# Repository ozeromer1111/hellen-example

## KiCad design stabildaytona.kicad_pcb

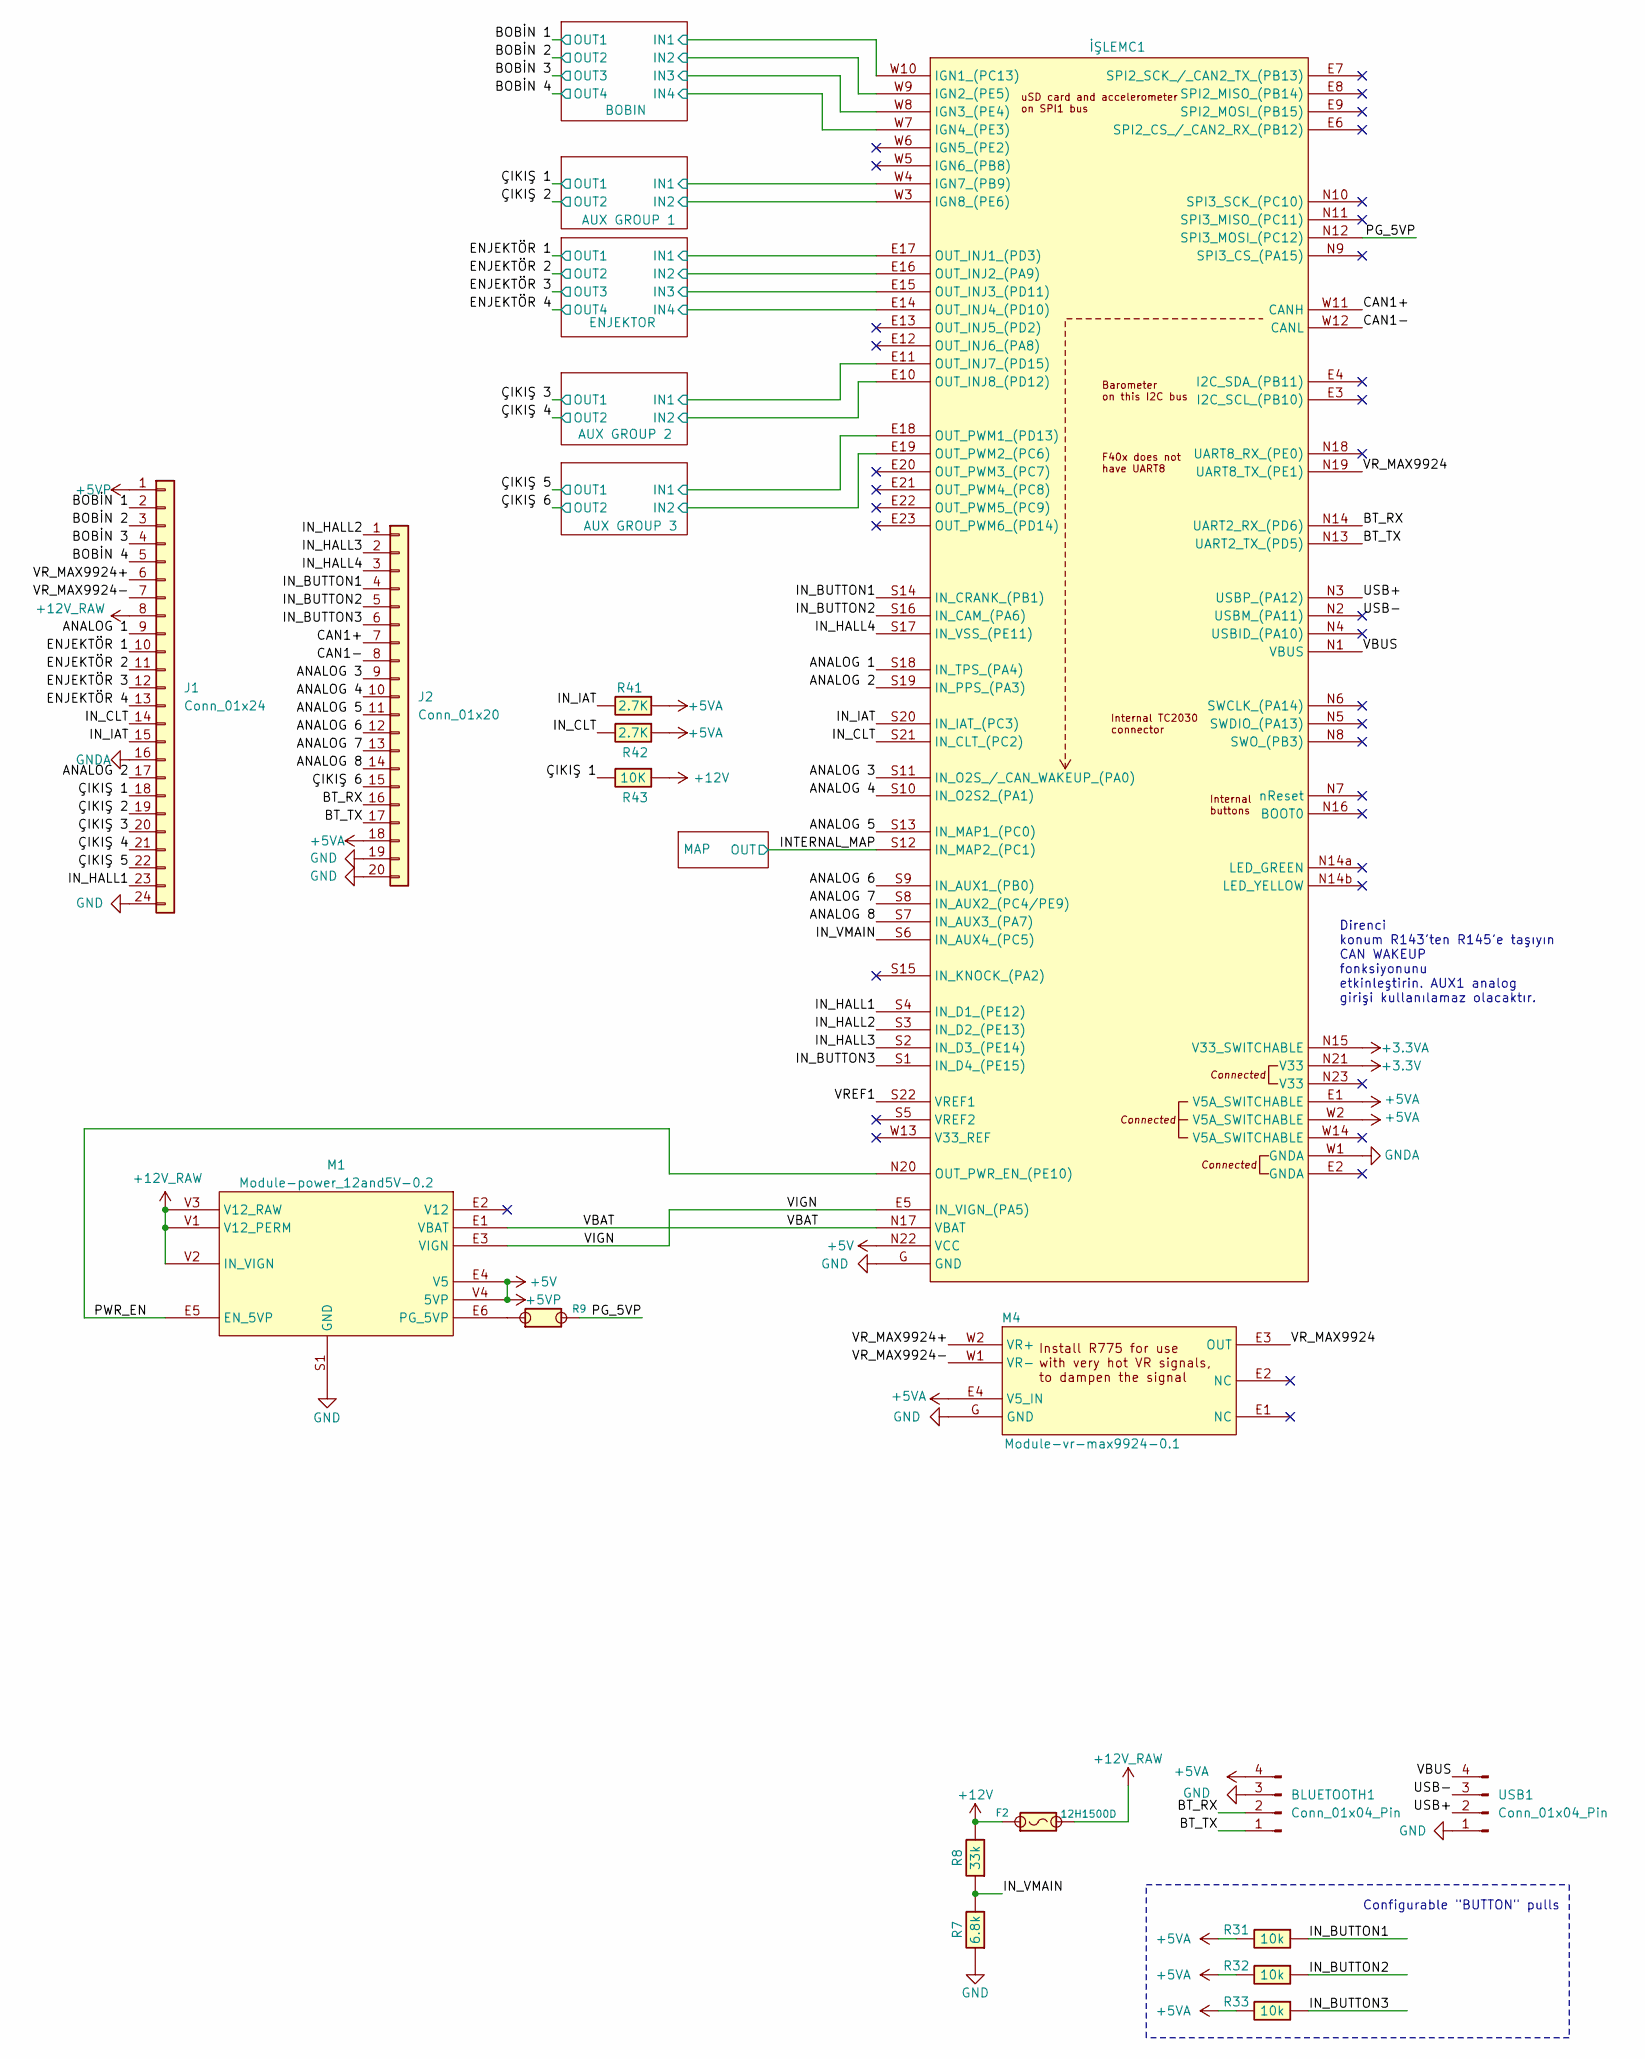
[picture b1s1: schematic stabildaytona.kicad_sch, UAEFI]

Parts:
BLUETOOTH1: Conn_01x04_Pin; PinSocket_1x04_P2.54mm_Vertical; LCSC C22438154
F2: 12H1500D; PAD-1206-PAD; LCSC C182446
J1: Conn_01x24; 24pin
J2: Conn_01x20; TE_2-826576-0_1x20_P3.96mm_Vertical
M1: Module-power_12and5V-0.2; power_12and5V
M4: Module-vr-max9924-0.1; vr-max9924
R7: 6.8k; R0603; LCSC C23212
R8: 33k; R0603; LCSC C4216
R9: Jumper-Pad-Pad; PAD-0805-PAD; LCSC C17477
R31, R32, R33: 10k; R0805; LCSC C17414
R41, R42: 2.7K; R0805; LCSC C17414
R43: 10K; R0805; LCSC C17414
USB1: Conn_01x04_Pin; JST_PH_B4B-PH-K_1x04_P2.00mm_Vertical; LCSC C265289
İŞLEMC1: Module:mega-mcu100/0.3; mega-mcu100

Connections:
+3.3V: İŞLEMC1.N21 (V33)
+3.3VA: İŞLEMC1.N15 (V33_SWITCHABLE)
+5V: J1.1, M1.E4 (V5), M1.V4 (5VP), İŞLEMC1.N22 (VCC)
+5VA: BLUETOOTH1.4, J2.18, M4.E4 (V5_IN), R31.2, R32.2, R33.2, R41.1, R42.1, İŞLEMC1.E1 (V5A_SWITCHABLE), İŞLEMC1.W2 (V5A_SWITCHABLE); also elsewhere on the board
+12V: F2.1, R8.2, R43.1
+12V_RAW: F2.2, J1.8, M1.V1 (V12_PERM), M1.V2 (IN_VIGN), M1.V3 (V12_RAW)
/ANALOG 1: J1.9, İŞLEMC1.S18 (IN_TPS_(PA4))
/ANALOG 2: J1.17, İŞLEMC1.S19 (IN_PPS_(PA3))
/ANALOG 3: J2.9, İŞLEMC1.S11 (IN_O2S_/_CAN_WAKEUP_(PA0))
/ANALOG 4: J2.10, İŞLEMC1.S10 (IN_O2S2_(PA1))
/ANALOG 5: J2.11, İŞLEMC1.S13 (IN_MAP1_(PC0))
/ANALOG 6: J2.12, İŞLEMC1.S9 (IN_AUX1_(PB0))
/ANALOG 7: J2.13, İŞLEMC1.S8 (IN_AUX2_(PC4/PE9))
/ANALOG 8: J2.14, İŞLEMC1.S7 (IN_AUX3_(PA7))
/AUX GROUP 1/IN1: İŞLEMC1.W4 (IGN7_(PB9)); also elsewhere on the board
/AUX GROUP 1/IN2: İŞLEMC1.W3 (IGN8_(PE6)); also elsewhere on the board
/AUX GROUP 2/IN1: İŞLEMC1.E11 (OUT_INJ7_(PD15)); also elsewhere on the board
/AUX GROUP 2/IN2: İŞLEMC1.E10 (OUT_INJ8_(PD12)); also elsewhere on the board
/AUX GROUP 3/IN1: İŞLEMC1.E18 (OUT_PWM1_(PD13)); also elsewhere on the board
/AUX GROUP 3/IN2: İŞLEMC1.E19 (OUT_PWM2_(PC6)); also elsewhere on the board
/BOBIN/IN1: İŞLEMC1.W10 (IGN1_(PC13)); also elsewhere on the board
/BOBIN/IN2: İŞLEMC1.W9 (IGN2_(PE5)); also elsewhere on the board
/BOBIN/IN3: İŞLEMC1.W8 (IGN3_(PE4)); also elsewhere on the board
/BOBIN/IN4: İŞLEMC1.W7 (IGN4_(PE3)); also elsewhere on the board
/BOBİN 1: J1.2; also elsewhere on the board
/BOBİN 2: J1.3; also elsewhere on the board
/BOBİN 3: J1.4; also elsewhere on the board
/BOBİN 4: J1.5; also elsewhere on the board
/BT_RX: BLUETOOTH1.2, J2.16, İŞLEMC1.N14 (UART2_RX_(PD6))
/BT_TX: BLUETOOTH1.1, J2.17, İŞLEMC1.N13 (UART2_TX_(PD5))
/CAN1+: J2.7, İŞLEMC1.W11 (CANH)
/CAN1-: J2.8, İŞLEMC1.W12 (CANL)
/ENJEKTOR/IN1: İŞLEMC1.E17 (OUT_INJ1_(PD3)); also elsewhere on the board
/ENJEKTOR/IN2: İŞLEMC1.E16 (OUT_INJ2_(PA9)); also elsewhere on the board
/ENJEKTOR/IN3: İŞLEMC1.E15 (OUT_INJ3_(PD11)); also elsewhere on the board
/ENJEKTOR/IN4: İŞLEMC1.E14 (OUT_INJ4_(PD10)); also elsewhere on the board
/ENJEKTÖR 1: J1.10; also elsewhere on the board
/ENJEKTÖR 2: J1.11; also elsewhere on the board
/ENJEKTÖR 3: J1.12; also elsewhere on the board
/ENJEKTÖR 4: J1.13; also elsewhere on the board
/INTERNAL_MAP: İŞLEMC1.S12 (IN_MAP2_(PC1)); also elsewhere on the board
/IN_BUTTON1: J2.4, R31.1, İŞLEMC1.S14 (IN_CRANK_(PB1))
/IN_BUTTON2: J2.5, R32.1, İŞLEMC1.S16 (IN_CAM_(PA6))
/IN_BUTTON3: J2.6, R33.1, İŞLEMC1.S1 (IN_D4_(PE15))
/IN_CLT: J1.14, R42.2, İŞLEMC1.S21 (IN_CLT_(PC2))
/IN_HALL1: J1.23, İŞLEMC1.S4 (IN_D1_(PE12))
/IN_HALL2: J2.1, İŞLEMC1.S3 (IN_D2_(PE13))
/IN_HALL3: J2.2, İŞLEMC1.S2 (IN_D3_(PE14))
/IN_HALL4: J2.3, İŞLEMC1.S17 (IN_VSS_(PE11))
/IN_IAT: J1.15, R41.2, İŞLEMC1.S20 (IN_IAT_(PC3))
/IN_VMAIN: R7.2, R8.1, İŞLEMC1.S6 (IN_AUX4_(PC5))
/PG_5VP: R9.2, İŞLEMC1.N12 (SPI3_MOSI_(PC12))
/PWR_EN: M1.E5 (EN_5VP), İŞLEMC1.N20 (OUT_PWR_EN_(PE10))
/USB+: USB1.2, İŞLEMC1.N3 (USBP_(PA12))
/USB-: USB1.3, İŞLEMC1.N2 (USBM_(PA11))
/VBAT: M1.E1 (VBAT), İŞLEMC1.N17 (VBAT)
/VBUS: USB1.4, İŞLEMC1.N1 (VBUS)
/VIGN: M1.E3 (VIGN), İŞLEMC1.E5 (IN_VIGN_(PA5))
/VREF1: İŞLEMC1.S22 (VREF1)
/VR_MAX9924: M4.E3 (OUT), İŞLEMC1.N19 (UART8_TX_(PE1))
/VR_MAX9924+: J1.6, M4.W2 (VR+)
/VR_MAX9924-: J1.7, M4.W1 (VR-)
/ÇIKIŞ 1: J1.18, R43.2; also elsewhere on the board
/ÇIKIŞ 2: J1.19; also elsewhere on the board
/ÇIKIŞ 3: J1.20; also elsewhere on the board
/ÇIKIŞ 4: J1.21; also elsewhere on the board
/ÇIKIŞ 5: J1.22; also elsewhere on the board
/ÇIKIŞ 6: J2.15; also elsewhere on the board
GND: BLUETOOTH1.3, J1.24, J2.19, J2.20, M1.S1 (GND), M4.G (GND), R7.1, USB1.1, İŞLEMC1.G (GND); also elsewhere on the board
GNDA: J1.16, İŞLEMC1.W1 (GNDA)
unnamed: M1.E6 (PG_5VP), R9.1

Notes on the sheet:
Direnci konum R143'ten R145'e taşıyın CAN WAKEUP fonksiyonunu etkinleştirin. AUX1 analog girişi kullanılamaz olacaktır.
Configurable "BUTTON" pulls

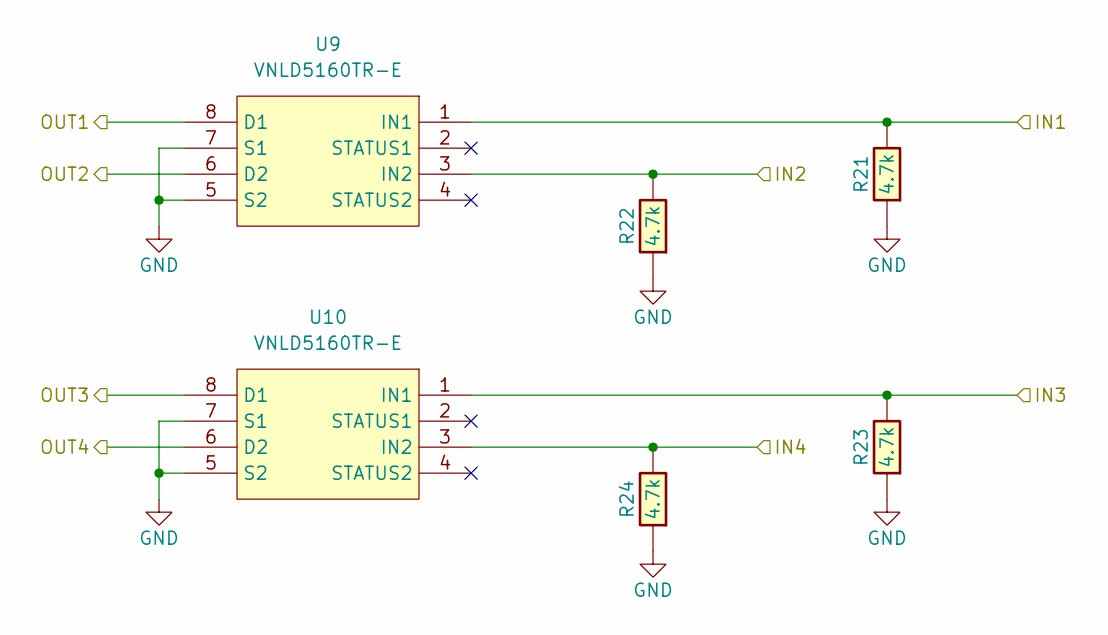
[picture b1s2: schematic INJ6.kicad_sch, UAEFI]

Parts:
R21, R22, R23, R24: 4.7k; R0603; LCSC C23162
U9, U10: VNLD5160TR-E; SOIC-8_3.9x4.9mm_P1.27mm; LCSC C377942

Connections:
/ENJEKTOR/IN1: R21.2, U9.1 (IN1); also elsewhere on the board
/ENJEKTOR/IN2: R22.2, U9.3 (IN2); also elsewhere on the board
/ENJEKTOR/IN3: R23.2, U10.1 (IN1); also elsewhere on the board
/ENJEKTOR/IN4: R24.2, U10.3 (IN2); also elsewhere on the board
/ENJEKTÖR 1: U9.8 (D1); also elsewhere on the board
/ENJEKTÖR 2: U9.6 (D2); also elsewhere on the board
/ENJEKTÖR 3: U10.8 (D1); also elsewhere on the board
/ENJEKTÖR 4: U10.6 (D2); also elsewhere on the board
GND: R21.1, R22.1, R23.1, R24.1, U9.5 (S2), U9.7 (S1), U10.5 (S2), U10.7 (S1); also elsewhere on the board

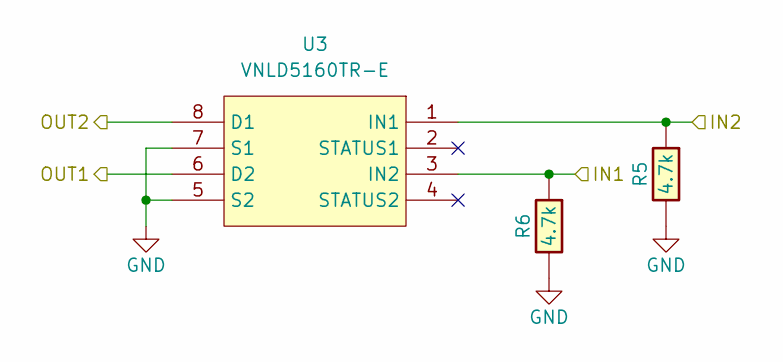
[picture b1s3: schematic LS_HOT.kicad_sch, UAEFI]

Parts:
R5, R6: 4.7k; R0603; LCSC C23162
U3: VNLD5160TR-E; SOIC-8_3.9x4.9mm_P1.27mm; LCSC C377942

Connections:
/AUX GROUP 3/IN1: R6.1, U3.3 (IN2); also elsewhere on the board
/AUX GROUP 3/IN2: R5.1, U3.1 (IN1); also elsewhere on the board
/ÇIKIŞ 5: U3.6 (D2); also elsewhere on the board
/ÇIKIŞ 6: U3.8 (D1); also elsewhere on the board
GND: R5.2, R6.2, U3.5 (S2), U3.7 (S1); also elsewhere on the board

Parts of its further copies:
R1, R2, R3, R4: 4.7k; R0603; LCSC C23162
U1, U2: VNLD5160TR-E; SOIC-8_3.9x4.9mm_P1.27mm; LCSC C377942

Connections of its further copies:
/AUX GROUP 1/IN1: R2.1, U1.3 (IN2); also elsewhere on the board
/AUX GROUP 1/IN2: R1.1, U1.1 (IN1); also elsewhere on the board
/AUX GROUP 2/IN1: R4.1, U2.3 (IN2); also elsewhere on the board
/AUX GROUP 2/IN2: R3.1, U2.1 (IN1); also elsewhere on the board
/ÇIKIŞ 1: U1.6 (D2); also elsewhere on the board
/ÇIKIŞ 2: U1.8 (D1); also elsewhere on the board
/ÇIKIŞ 3: U2.6 (D2); also elsewhere on the board
/ÇIKIŞ 4: U2.8 (D1); also elsewhere on the board
GND: R1.2, R2.2, R3.2, R4.2, U1.5 (S2), U1.7 (S1), U2.5 (S2), U2.7 (S1); also elsewhere on the board

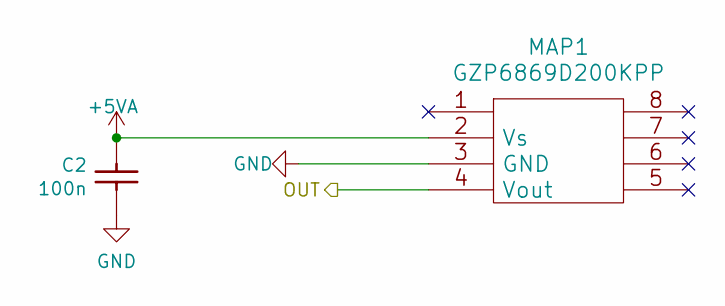
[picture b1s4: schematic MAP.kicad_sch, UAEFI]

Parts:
C2: 100n; C0603; LCSC C14663
MAP1: GZP6869D200KPP; MPXH6400A-SSOP8; LCSC C3038053

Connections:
+5VA: MAP1.2 (Vs); also elsewhere on the board
/INTERNAL_MAP: MAP1.4 (Vout); also elsewhere on the board
GND: MAP1.3 (GND); also elsewhere on the board

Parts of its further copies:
C1: 100n; C0603; LCSC C14663

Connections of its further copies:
+5VA: C1.2; also elsewhere on the board
GND: C1.1; also elsewhere on the board

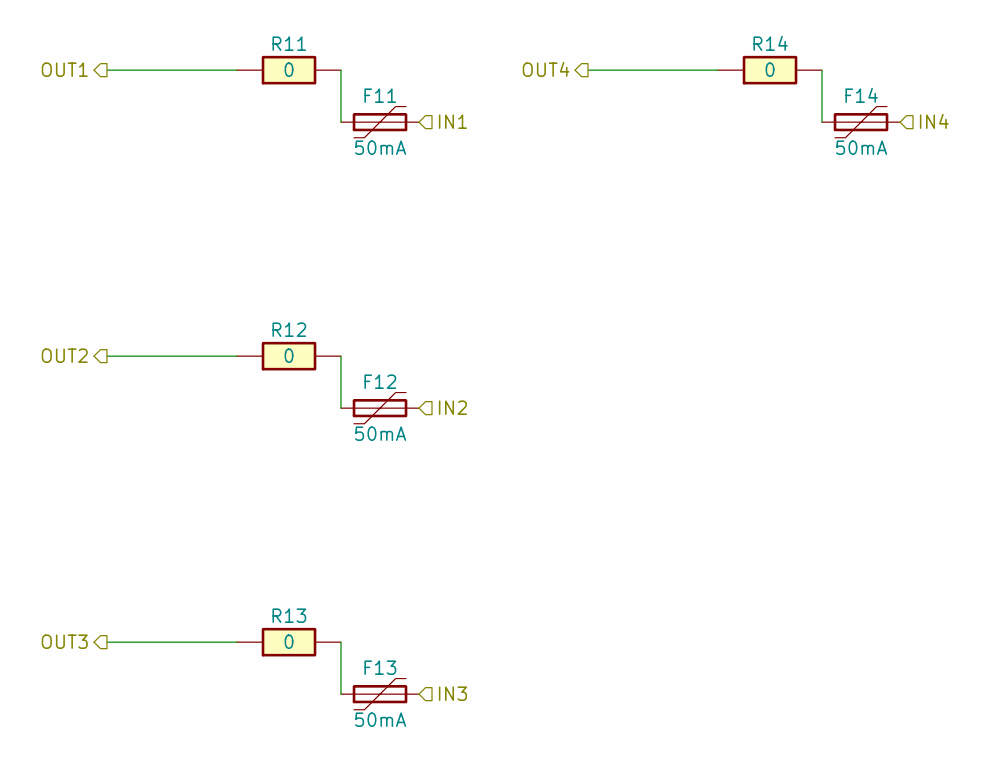
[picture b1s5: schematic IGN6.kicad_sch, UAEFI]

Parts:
F11, F12, F13, F14: 50mA; Fuse_0603_1608Metric; LCSC C369141
R11, R12, R13, R14: 0; R0603; LCSC C21189

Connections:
/BOBIN/IN1: F11.2; also elsewhere on the board
/BOBIN/IN2: F12.2; also elsewhere on the board
/BOBIN/IN3: F13.2; also elsewhere on the board
/BOBIN/IN4: F14.2; also elsewhere on the board
/BOBİN 1: R11.1; also elsewhere on the board
/BOBİN 2: R12.1; also elsewhere on the board
/BOBİN 3: R13.1; also elsewhere on the board
/BOBİN 4: R14.1; also elsewhere on the board
unnamed: F11.1, R11.2
unnamed: F12.1, R12.2
unnamed: F13.1, R13.2
unnamed: F14.1, R14.2

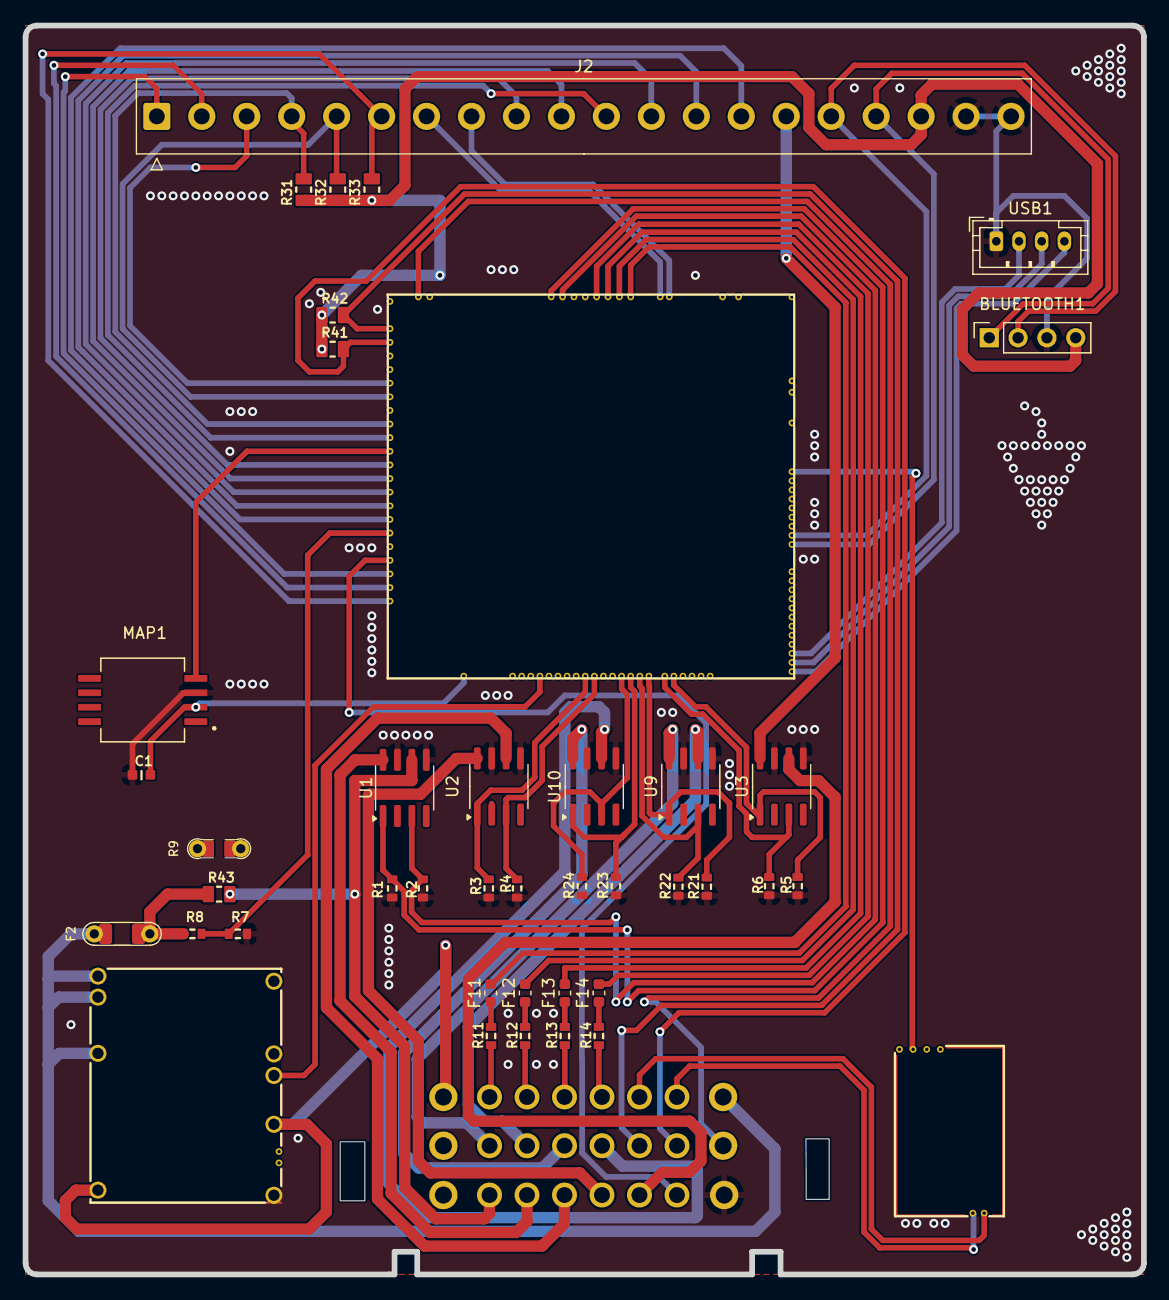
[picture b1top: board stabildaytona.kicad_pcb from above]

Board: 4 copper layers, 98.5 x 110.0 mm, 42 parts (0 on the bottom side), 72 nets.

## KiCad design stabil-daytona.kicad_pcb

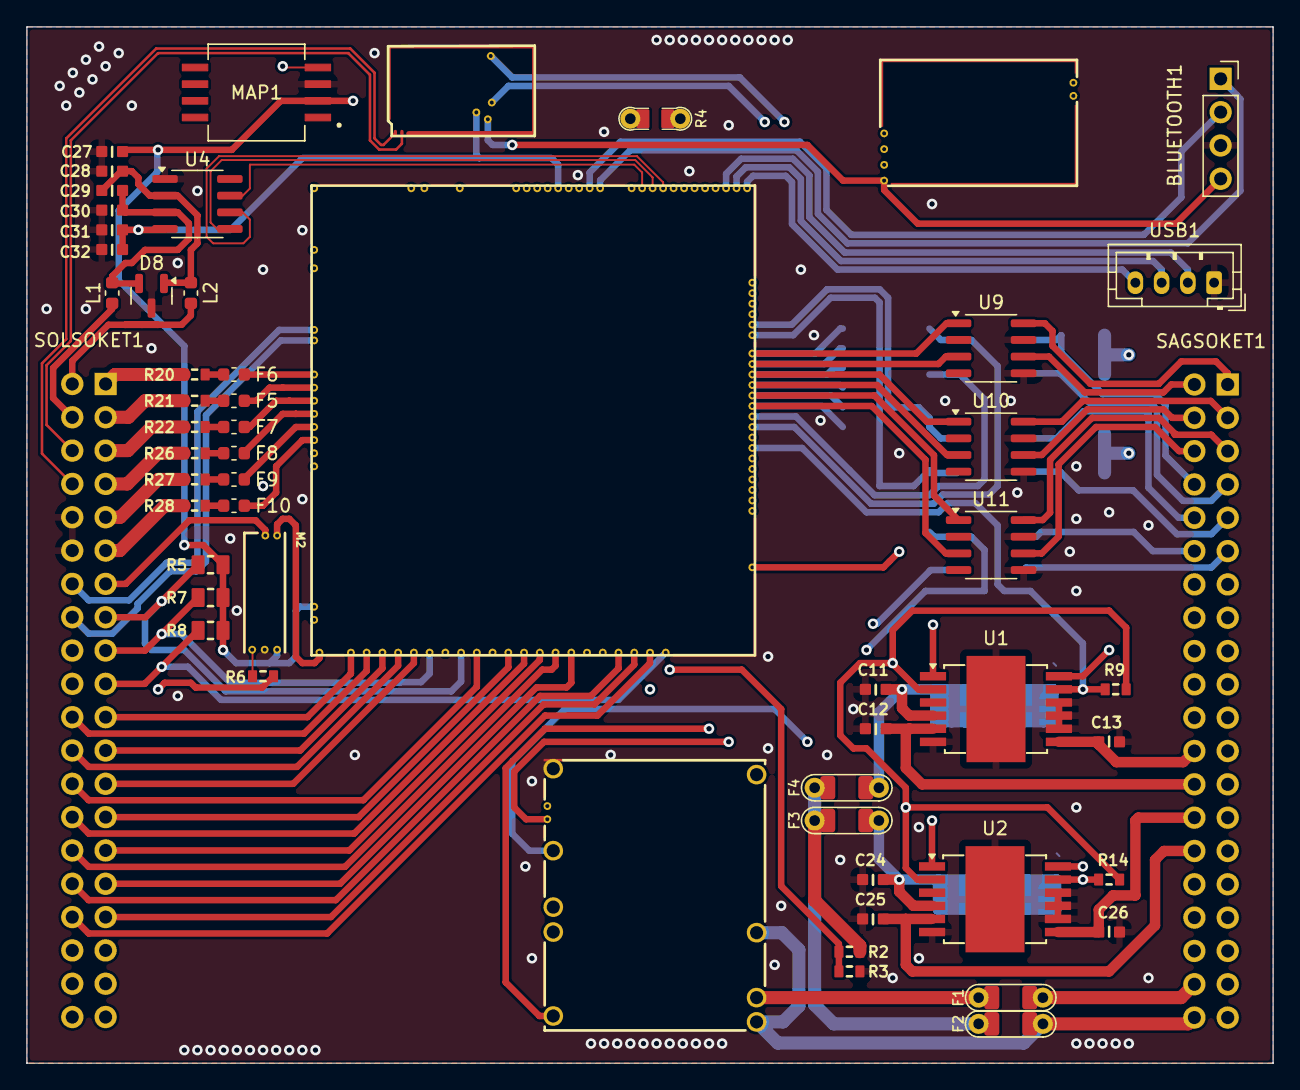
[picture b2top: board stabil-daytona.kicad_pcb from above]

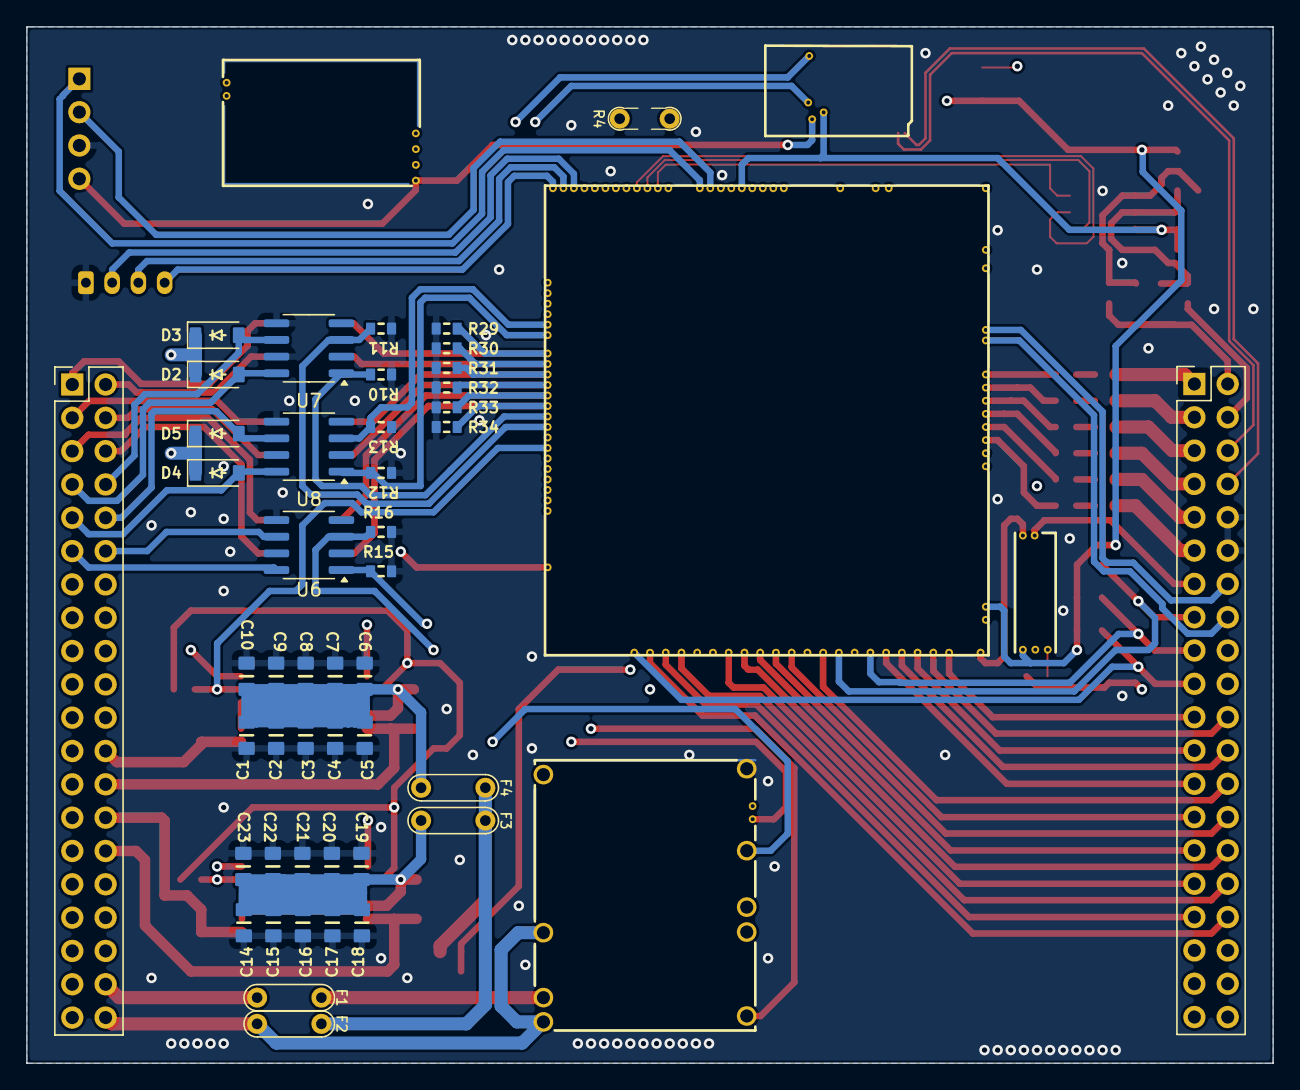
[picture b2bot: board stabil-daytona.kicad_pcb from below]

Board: 4 copper layers, 95.0 x 79.0 mm, 97 parts (41 on the bottom side), 114 nets.

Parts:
BLUETOOTH1: Conn_01x04_Pin; PinSocket_1x04_P2.54mm_Vertical
C1, C2, C3, C4, C5, C6, C7, C8, C9, C10, C14, C15, C16, C17, C18, C19, C20, C21, C22, C23: 10u; C0805
C11, C24, C27, C29, C31: 100n; C0603
C12, C13, C25, C26, C28, C30: 10n; C0603
C32: 1u; C0603
CAN1: Module-can-0.1; can
D2, D3, D4, D5: B5819W; SOD-123
D8: NUP2105L; SOT-23
F1, F2, F3, F4: 12H1500D; PAD-1206-PAD
F5, F6, F7, F8, F9, F10: 50mA; Fuse_0603_1608Metric
G1: RUSEFI_LOGO; rusefi_logo
G2: LOGO
L1, L2: 470R@100MHz; L_0603_1608Metric
M1: Module-power_12and5V-0.2; power_12and5V
M2: Module-knock-0.2; knock
M4: Module-vr-max9924-0.1; vr-max9924
MAP1: MPXH6400A; MPXH6400A-SSOP8
MCU1: Module:mega-mcu100/0.3; mega-mcu100
R2: 33k; R0603
R3: 6.8k; R0603
R4: Jumper-Pad-Pad; PAD-0805-PAD
R5, R7, R8: 10k; R0805
R6, R20, R21, R22, R26, R27, R28: 0; R0603
R9, R10, R11, R12, R13, R14, R15, R16, R29, R30, R31, R32, R33, R34: 4.7k; R0603
SAGSOKET1: Conn_02x20_Counter_Clockwise; PinHeader_2x20_P2.54mm_Vertical
SOLSOKET1: Conn_02x20_Counter_Clockwise; PinHeader_2x20_P2.54mm_Vertical
U1, U2: TLE9201SG; Infineon_PG-DSO-12-11
U4: MAX31855KASA; SOIC-8_3.9x4.9mm_P1.27mm
U6, U7, U8, U9, U10, U11: VNLD5160TR-E; SOIC-8_3.9x4.9mm_P1.27mm
USB1: Conn_01x04_Pin; JST_PH_B4B-PH-K_1x04_P2.00mm_Vertical

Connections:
+3.3V: MCU1.N21 (V33), R9.2, R14.2, U1.2 (VSO), U2.2 (VSO)
+3.3VA: C31.2, C32.2, CAN1.V2 (CAN_VIO), MCU1.N15 (V33_SWITCHABLE), U4.4 (V_CC)
+5V: M1.E4 (V5), MCU1.N22 (VCC)
+5VA: BLUETOOTH1.4, C27.2, CAN1.V1 (V5), M2.E1 (V5A), M4.E4 (V5_IN), MAP1.2 (Vs), MCU1.E1 (V5A_SWITCHABLE), MCU1.W2 (V5A_SWITCHABLE), R5.2, R7.2, R8.2
+5VP: M1.V4 (5VP), SOLSOKET1.18, SOLSOKET1.20
+12V: F2.1, F3.1, F4.1, R2.2
+12V_RAW: D2.1 (K), D3.1 (K), D4.1 (K), D5.1 (K), F2.2, M1.V1 (V12_PERM), M1.V3 (V12_RAW), SAGSOKET1.40
/12V_KEY: F1.1, SAGSOKET1.38
/ADC3: MCU1.S15 (IN_KNOCK_(PA2)), R6.2
/BT_RX: BLUETOOTH1.2, MCU1.N14 (UART2_RX_(PD6))
/BT_TX: BLUETOOTH1.1, MCU1.N13 (UART2_TX_(PD5))
/CAN1+: MCU1.W11 (CANH), SOLSOKET1.16
/CAN1-: MCU1.W12 (CANL), SOLSOKET1.14
/CAN2+: CAN1.S2 (CANH), SOLSOKET1.6
/CAN2-: CAN1.S1 (CANL), SOLSOKET1.8
/DC1_DIR: MCU1.E21 (OUT_PWM4_(PC8)), U1.1 (DIR)
/DC1_DIS: MCU1.E8 (SPI2_MISO_(PB14)), R9.1, U1.11 (DIS)
/DC1_PWM: MCU1.E20 (OUT_PWM3_(PC7)), U1.12 (PWM)
/DC2_DIR: MCU1.E9 (SPI2_MOSI_(PB15)), U2.1 (DIR)
/DC2_DIS: MCU1.N4 (USBID_(PA10)), R14.1, U2.11 (DIS)
/DC2_PWM: MCU1.E22 (OUT_PWM5_(PC9)), U2.12 (PWM)
/DC Driver 1/PWR: C1.2, C2.2, C3.2, C4.2, C5.2, C6.2, C7.2, C8.2, C9.2, C10.2, C11.2, F4.2, U1.4 (VS)
/DC Driver 2/PWR: C14.2, C15.2, C16.2, C17.2, C18.2, C19.2, C20.2, C21.2, C22.2, C23.2, C24.2, F3.2, U2.4 (VS)
/EGT+: L1.1, SOLSOKET1.4
/EGT-: L2.1, SOLSOKET1.2
/EGT/SPI_CS: MCU1.N9 (SPI3_CS_(PA15)), U4.6 (~CS)
/EGT/SPI_SCK: MCU1.N10 (SPI3_SCK_(PC10)), U4.5 (SCK)
/EGT/SPI_SO: MCU1.N11 (SPI3_MISO_(PC11)), U4.7 (SO)
/IGN1: F6.2, MCU1.W10 (IGN1_(PC13))
/IGN2: F5.2, MCU1.W9 (IGN2_(PE5))
/IGN3: F7.2, MCU1.W8 (IGN3_(PE4))
/IGN4: F8.2, MCU1.W7 (IGN4_(PE3))
/IGN5: F9.2, MCU1.W6 (IGN5_(PE2))
/IGN6: F10.2, MCU1.W5 (IGN6_(PB8))
/INJ1: MCU1.E17 (OUT_INJ1_(PD3)), R29.2, U9.1 (IN1)
/INJ2: MCU1.E16 (OUT_INJ2_(PA9)), R30.2, U9.3 (IN2)
/INJ3: MCU1.E15 (OUT_INJ3_(PD11)), R31.2, U10.1 (IN1)
/INJ4: MCU1.E14 (OUT_INJ4_(PD10)), R32.2, U10.3 (IN2)
/INJ5: MCU1.E13 (OUT_INJ5_(PD2)), R33.2, U11.1 (IN1)
/INJ6: MCU1.E12 (OUT_INJ6_(PA8)), R34.2, U11.3 (IN2)
/INTERNAL_MAP: MAP1.4 (Vout), MCU1.S12 (IN_MAP2_(PC1))
/IN_AUX1: MCU1.S11 (IN_O2S_/_CAN_WAKEUP_(PA0)), SOLSOKET1.27
/IN_AUX2: MCU1.S10 (IN_O2S2_(PA1)), SOLSOKET1.28
/IN_AUX3: MCU1.S7 (IN_AUX3_(PA7)), SOLSOKET1.31
/IN_BUTTON1: MCU1.S14 (IN_CRANK_(PB1)), R5.1, SOLSOKET1.15
/IN_BUTTON2: MCU1.S16 (IN_CAM_(PA6)), R7.1, SOLSOKET1.17
/IN_BUTTON3: MCU1.S1 (IN_D4_(PE15)), R8.1, SOLSOKET1.19
/IN_CLT: MCU1.S21 (IN_CLT_(PC2)), SOLSOKET1.21
/IN_FLEX: MCU1.S17 (IN_VSS_(PE11)), SOLSOKET1.25
/IN_HALL1: MCU1.S4 (IN_D1_(PE12)), SOLSOKET1.32
/IN_HALL2: MCU1.S3 (IN_D2_(PE13)), SOLSOKET1.33
/IN_HALL3: MCU1.S2 (IN_D3_(PE14)), SOLSOKET1.34
/IN_IAT: MCU1.S20 (IN_IAT_(PC3)), SOLSOKET1.22
/IN_KNOCK: M2.E3 (OUT_KNOCK), R6.1
/IN_KNOCK_RAW: M2.W1 (IN_KNOCK), SOLSOKET1.13
/IN_MAP: MCU1.S13 (IN_MAP1_(PC0)), SOLSOKET1.26
/IN_PPS1: MCU1.S19 (IN_PPS_(PA3)), SOLSOKET1.23
/IN_PPS2: MCU1.S8 (IN_AUX2_(PC4/PE9)), SOLSOKET1.30
/IN_TPS1: MCU1.S18 (IN_TPS_(PA4)), SOLSOKET1.24
/IN_TPS2: MCU1.S9 (IN_AUX1_(PB0)), SOLSOKET1.29
/IN_VIGN: F1.2, M1.V2 (IN_VIGN)
/IN_VMAIN: MCU1.S6 (IN_AUX4_(PC5)), R2.1, R3.2
/LS1: MCU1.E11 (OUT_INJ7_(PD15)), R10.2, U7.1 (IN1)
/LS2: MCU1.E10 (OUT_INJ8_(PD12)), R11.2, U7.3 (IN2)
/LS3: MCU1.E18 (OUT_PWM1_(PD13)), R12.2, U8.1 (IN1)
/LS4: MCU1.E19 (OUT_PWM2_(PC6)), R13.2, U8.3 (IN2)
/LS_HOT1: MCU1.W4 (IGN7_(PB9)), R16.1, U6.3 (IN2)
/LS_HOT2: MCU1.W3 (IGN8_(PE6)), R15.1, U6.1 (IN1)
/MCU-CAN2RX: CAN1.V6 (CAN_RX), MCU1.E6 (SPI2_CS_/_CAN2_RX_(PB12))
/MCU-CAN2TX: CAN1.V5 (CAN_TX), MCU1.E7 (SPI2_SCK_/_CAN2_TX_(PB13))
/OUT_DC1+: C13.2, SAGSOKET1.24, U1.7 (OUT2)
/OUT_DC1-: C12.2, SAGSOKET1.26, U1.5 (OUT1)
/OUT_DC2+: C26.2, SAGSOKET1.28, U2.7 (OUT2)
/OUT_DC2-: C25.2, SAGSOKET1.30, U2.5 (OUT1)
/OUT_IGN1: R20.1, SOLSOKET1.1
/OUT_IGN2: R21.1, SOLSOKET1.3
/OUT_IGN3: R22.1, SOLSOKET1.5
/OUT_IGN4: R26.1, SOLSOKET1.7
/OUT_IGN5: R27.1, SOLSOKET1.9
/OUT_IGN6: R28.1, SOLSOKET1.11
/OUT_INJ1: SAGSOKET1.1, U9.8 (D1)
/OUT_INJ2: SAGSOKET1.2, U9.6 (D2)
/OUT_INJ3: SAGSOKET1.3, U10.8 (D1)
/OUT_INJ4: SAGSOKET1.4, U10.6 (D2)
/OUT_INJ5: SAGSOKET1.5, U11.8 (D1)
/OUT_INJ6: SAGSOKET1.6, U11.6 (D2)
/OUT_LS1: D2.2 (A), SAGSOKET1.7, U7.8 (D1)
/OUT_LS2: D3.2 (A), SAGSOKET1.8, U7.6 (D2)
/OUT_LS3: D4.2 (A), SAGSOKET1.9, U8.8 (D1)
/OUT_LS4: D5.2 (A), SAGSOKET1.10, U8.6 (D2)
/OUT_LS_HOT1: SAGSOKET1.12, U6.6 (D2)
/OUT_LS_HOT2: SAGSOKET1.11, U6.8 (D1)
/PG_5VP: MCU1.N12 (SPI3_MOSI_(PC12)), R4.2
/PWR_EN: M1.E5 (EN_5VP), MCU1.N20 (OUT_PWR_EN_(PE10))
/USB+: MCU1.N3 (USBP_(PA12)), USB1.2
/USB-: MCU1.N2 (USBM_(PA11)), USB1.3
/VBAT: M1.E1 (VBAT), MCU1.N17 (VBAT)
/VBUS: MCU1.N1 (VBUS), USB1.4
/VIGN: M1.E3 (VIGN), MCU1.E5 (IN_VIGN_(PA5))
/VREF1: M2.W2 (VREF), MCU1.S22 (VREF1)
/VR_MAX9924: M4.E3 (OUT), MCU1.N19 (UART8_TX_(PE1))
/VR_MAX9924+: M4.W2 (VR+), SAGSOKET1.14
/VR_MAX9924-: M4.W1 (VR-), SAGSOKET1.16
GND: BLUETOOTH1.3, C1.1, C2.1, C3.1, C4.1, C5.1, C6.1, C7.1, C8.1, C9.1, C10.1, C11.1, C12.1, C13.1, C14.1, C15.1, C16.1, C17.1, C18.1, C19.1, C20.1, C21.1, C22.1, C23.1, C24.1, C25.1, C26.1, C27.1, C28.1, C30.1, C31.1, C32.1, CAN1.E1 (GND), D8.3 (A), M1.S1 (GND), M2.E2 (GND), M4.G (GND), MAP1.3 (GND), MCU1.G (GND), R3.1, R10.1, R11.1, R12.1, R13.1, R15.2, R16.2, R29.1, R30.1, R31.1, R32.1, R33.1, R34.1, SOLSOKET1.10, SOLSOKET1.12, U1.6 (GND), U1.8 (SI), U1.9 (CSN), U1.10 (SCK), U1.13 (GND), U2.6 (GND), U2.8 (SI), U2.9 (CSN), U2.10 (SCK), U2.13 (GND), U4.1 (GND), U6.5 (S2), U6.7 (S1), U7.5 (S2), U7.7 (S1), U8.5 (S2), U8.7 (S1), U9.5 (S2), U9.7 (S1), U10.5 (S2), U10.7 (S1), U11.5 (S2), U11.7 (S1), USB1.1
GNDA: MCU1.W1 (GNDA), SOLSOKET1.35, SOLSOKET1.36
unnamed: F5.1, R21.2
unnamed: F6.1, R20.2
unnamed: F7.1, R22.2
unnamed: F8.1, R26.2
unnamed: F9.1, R27.2
unnamed: F10.1, R28.2
unnamed: M1.E6 (PG_5VP), R4.1
unnamed: C29.2, C30.2, D8.2 (K), L1.2, U4.3 (T+)
unnamed: C28.2, C29.1, D8.1 (K), L2.2, U4.2 (T-)

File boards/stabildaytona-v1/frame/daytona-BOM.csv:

Comment,Designator,Footprint,LCSC Part #
"Conn_01x04_Pin","BLUETOOTH1","PinSocket_1x04_P2.54mm_Vertical","C22438154"
"10u","C1","C0805","C15850"
"10u","C2","C0805","C15850"
"10u","C3","C0805","C15850"
"10u","C4","C0805","C15850"
"10u","C5","C0805","C15850"
"10u","C6","C0805","C15850"
"10u","C7","C0805","C15850"
"10u","C8","C0805","C15850"
"10u","C9","C0805","C15850"
"10u","C10","C0805","C15850"
"100n","C11","C0603","C14663"
"10n","C12","C0603","C57112"
"10n","C13","C0603","C57112"
"10u","C14","C0805","C15850"
"10u","C15","C0805","C15850"
"10u","C16","C0805","C15850"
"10u","C17","C0805","C15850"
"10u","C18","C0805","C15850"
"10u","C19","C0805","C15850"
"10u","C20","C0805","C15850"
"10u","C21","C0805","C15850"
"10u","C22","C0805","C15850"
"10u","C23","C0805","C15850"
"100n","C24","C0603","C14663"
"10n","C25","C0603","C57112"
"10n","C26","C0603","C57112"
"100n","C27","C0603","C14663"
"10n","C28","C0603","C57112"
"100n","C29","C0603","C14663"
"10n","C30","C0603","C57112"
"100n","C31","C0603","C14663"
"1u","C32","C0603","C15849"
"Module:can/0.1","CAN1","can",""
"B5819W","D2","SOD-123","C8598"
"B5819W","D3","SOD-123","C8598"
"B5819W","D4","SOD-123","C8598"
"B5819W","D5","SOD-123","C8598"
"NUP2105L","D8","SOT-23","C284104"
"12H1500D","F1","PAD-1206-PAD","C182446"
"12H1500D","F2","PAD-1206-PAD","C182446"
"12H1500D","F3","PAD-1206-PAD","C182446"
"12H1500D","F4","PAD-1206-PAD","C182446"
"50mA","F5","Fuse_0603_1608Metric","C369141"
"50mA","F6","Fuse_0603_1608Metric","C369141"
"50mA","F7","Fuse_0603_1608Metric","C369141"
"50mA","F8","Fuse_0603_1608Metric","C369141"
"50mA","F9","Fuse_0603_1608Metric","C369141"
"50mA","F10","Fuse_0603_1608Metric","C369141"
"470R@100MHz","L1","L_0603_1608Metric","C97853"
"470R@100MHz","L2","L_0603_1608Metric","C97853"
"Module:power_12and5V/0.2","M1","power_12and5V",""
"Module:knock/0.2","M2","knock",""
"Module:vr-max9924/0.1","M4","vr-max9924",""
"MPXH6400A","MAP1","MPXH6400A-SSOP8","C511770"
"Module:mega-mcu100/0.3","MCU1","mega-mcu100",""
"33k","R2","R0603","C4216"
"6.8k","R3","R0603","C23212"
"Jumper-Pad-Pad","R4","PAD-0805-PAD","C17477"
"10k","R5","R0805","C17414"
"0","R6","R0603","C21189"
"10k","R7","R0805","C17414"
"10k","R8","R0805","C17414"
"4.7k","R9","R0603","C23162"
"4.7k","R10","R0603","C23162"
"4.7k","R11","R0603","C23162"
"4.7k","R12","R0603","C23162"
"4.7k","R13","R0603","C23162"
"4.7k","R14","R0603","C23162"
"4.7k","R15","R0603","C23162"
"4.7k","R16","R0603","C23162"
"0","R20","R0603","C21189"
"0","R21","R0603","C21189"
"0","R22","R0603","C21189"
"0","R26","R0603","C21189"
"0","R27","R0603","C21189"
"0","R28","R0603","C21189"
"4.7k","R29","R0603","C23162"
"4.7k","R30","R0603","C23162"
"4.7k","R31","R0603","C23162"
"4.7k","R32","R0603","C23162"
"4.7k","R33","R0603","C23162"
"4.7k","R34","R0603","C23162"
"Conn_02x20_Counter_Clockwise","SAGSOKET1","PinHeader_2x20_P2.54mm_Vertical","C19630948"
"Conn_02x20_Counter_Clockwise","SOLSOKET1","PinHeader_2x20_P2.54mm_Vertical","C19630948"
"TLE9201SG","U1","Infineon_PG-DSO-12-11","C112633"
"TLE9201SG","U2","Infineon_PG-DSO-12-11","C112633"
"MAX31855KASA","U4","SO8","C52028"
"VNLD5160TR-E","U6","SO8","C377942"
"VNLD5160TR-E","U7","SO8","C377942"
"VNLD5160TR-E","U8","SO8","C377942"
"VNLD5160TR-E","U9","SO8","C377942"
"VNLD5160TR-E","U10","SO8","C377942"
"VNLD5160TR-E","U11","SO8","C377942"
"Conn_01x04_Pin","USB1","JST_PH_B4B-PH-K_1x04_P2.00mm_Vertical","C265289"

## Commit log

2024-12-31 v1
    stabil daytona v1
2025-01-02 v1 test
    test
2025-01-02 test v2
    v2
2025-01-02 [skip actions] Auto-generated board v2.1
2025-01-02 GHA says update hellen-one
2025-01-02 test v3
2025-01-02 test v4
2025-01-03 v1 tam test
2025-01-31 GHA says update kicad6-libraries
2025-04-19 stabil jr.
